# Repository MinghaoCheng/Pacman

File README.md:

# Pacman
ENG5220, Embedded real-time programming project, Team19

|Author|Team 19|
|---|---
|E-mail|2359434c@student.gla.ac.uk

* The follwing link is two demostrations of playing the game, catched by the ghost and won the game
https://www.youtube.com/playlist?list=PLmhQhGby8E4eoPKThM3S1RnaBH7sxEcJI

## Motivation& Introduction

As a classic computer game, Pacman impressed lots of people. Now we can do a Pacman game in real life!

This project uses a game panel which contains two 4x4 LED matrices. One of them is in green working as Pacdots, and the other one is in red to represent the Ghost. There is also a 4x4 LDR matrix to give feedback to the host. Three matrices are on the same place and controlled by the host raspberryPi.

There is a car controlled by a raspberryPi which acts as Pacman. It can move around upon the pannel, eat Pacdots and hide from the Ghost.

## Table of contents
* [Getting started](#getting_started)
* [System overview](#system_overview)
* [Required components(BOM)](#required_components(BOM))
* [Assemble](#assemble)
* [Software](#software)
* [Found a bug](#found_a_bug)
* [License](#license)
## Getting started 
1. Buiding hardware  
      Hardware contains PCBs, mechanics, sodering, see [Hardware](#hardware) for details.  
2. Built& install software  
    1. Host  
      To build the software of host: on host raspberryPi, type ```./build_host.sh``` in terminal.  
      To install the software of host:type ```sudo ./install_host.sh``` in terminal. (Only the kernel module needs to be installed)  
    2. Car  
      To build the software of car: on car raspberryPi, type ```./build_car.sh``` in terminal.
3. Execute the programme  
    1. Host  
      Type "sudo ./host_exe" in terminal. (Because this programme would access the kernel module, so it requires super_user)  
    2. Car  
      Type "./car_exe" in terminal.
4. Game rules  
      Once the game starts(After the background music), the Pacdots(green LEDs) would all be on. The Pacman(the Car) would follow the instructions of keyboard connected to the host. If the Pacman eats a Pacdot (car hits the green LED), the LDR would give feedback to the host and shut down the corresponding LED. Meanwhile, a sound would give the player a feedback. The player would win the game when all Pacdots are eaten (a winning music would be played). There is only one ghost(red LED), which would move randomly, if the Pacman hits the ghost, the player will lose (a losing music would be played).  
5. Have fun!  

## System overview
* This project contains a host and a car. The host does the following work:  
    ** Control a red LED matrix using a GPIO extender "MCP23S17" to display the location of the ghost
    ** Control a green LED matrix using a GPIO extender "MCP23S17" to display the pacdots
    ** Control a LDR matrix as the feedback of location of the car
    ** Handle a TCP/IP connection as the server, and send instructions to the car via the connection
    ** Connect with a simple keyboard as input
    ** Output sound through 3.5mm audio jack (Using function "system()" now, I would add ALSA sound driver later)  
* The car work as follow:
    ** Handle a TCP/IP connection as client to receive instructions from the host
    ** Control two motors(which drive the wheels of the car) through a dual H-bridge IC "L298N"
    ** The car sink current from 4xAA batteries and a 5V3A LDO is used.

## Required components(BOM)
* host_0 board

|Component|Quantity|Farnell code|
|---|---|---
|4816P-T02-222LF|1|2908136
|LM2901D|4|1648673
|Resistor,2kΩ,R0805|1|1469887
|Resistor,10kΩ,R0805|2|1469856
|MCP23S17T-E/SS|1|2775058
|pin header 2x8, bended, 2.54mm|2|2984492
|Capacitor, 0.1uF, C0603|1|2280842
|M20-6102045,Connector|1|1569230

* host_1 board

|Component|Quantity|Farnell code|
|---|---|---
|MCP23S17T-E/SS|1|2775058
|BCW66GLT1G|4|2317524
|BCW68GLT1G|4|2317538
|4816P-1-102LF|2|1612549
|M20-6102045,Connector|1|1569230
|pin header 2x8, bended, 2.54mm|1|2984492
|Capacitor, 0.1uF, C0603|1|2280842
|Resistor,200Ω,R0805*|8|1894175

    *:optional,depends on the impedence of the LEDs  

* car_0 board

|Component|Quantity|Farnell code|
|---|---|---
|L298N|1|403295
|NCP59301DS50R4G|1|2774711
|BYG10M-E3/TR|8|9549170
|Capacitor, 0.1uF, C0805|2|

* Others

|Component|Quantity|Farnell code|
|---|---|---
|RapsberryPi model 3B|2|
|Green LED*|16|
|Red LED*|16|
|LDR|16|3168335
|Wires|N/A|
|Panel**|1|

    *:could use any LEDs under 100mA, but the resistors on host_1 board needs to be adjusted  
    **:In this project, the panel was made of a cardboard.
## Assemble
* For PCBs of the host, connect them in the way as follow:  

<div align=center></div>  

<div align=center></div>  

* For LED&LDR matrices, put one green LED, one red LED and one LDR at a single hole on the panel(There are 4x4 holes). Note to put LDR above the LEDs.  

<div align=center></div>  

* Solder green LED matrix/red LED matrix as follow, this schematic also can be found at [PCBs](/Docs/PCBs):

<div align=center></div> 

* Solder keyboard following the schematic

* Picture of the system set

<div align=center></div>

<div align=center></div>

## Software
* There are two source codes in this project. One works on the host and another one works on the car.  
* The software of the host contains a kernel module which would work as the driver of the GPIO(it handles GPIO interrupt and output of the GPIO used by the host), and it contains the main codes which works in the user space. There are several components of this software, see details at [Docs](/Docs/software/host)  
* The software of the car controls the motor using L298N through GPIO, and it also receives instructions from the host over TCP/IP through Wi-Fi connection. See details at [Docs](/Docs/software/car)   
* dependency:  
      * host:
      ```pthread, rt, ```
      * car:
      ```pthread```
## Found a bug<a name="found_a_bug">
* Hardware:  
      To isolate the fault of the hardware, the best way is to check the PCB-layouts and schematics.  
      Here is the definition of pins used by the host:  
      
|Raspi-pin|Function|
|---|---
|03|Reset of MCP23S17(s)
|05|INT B of MCP23S17 of LDR board
|07|INT A of MCP23S17 of LDR board
|19|MOSI of SPI bus
|21|MISO of SPI bus
|23|CLK of SPI bus
|24|CS_0 of SPI bus, LDR board
|26|CS_1 of SPI bus, LED board
|29|Keyboard, Left
|31|Keyboard, Up
|33|Keyboard, Right
|35|Keyboard, Down
|37|Keyboard, Reset
      
* Software:
      Remember to add "sudo" to install the host kernel module and execute the programme
      
* For other questions, you can send me an Email with description

## License
See license.md

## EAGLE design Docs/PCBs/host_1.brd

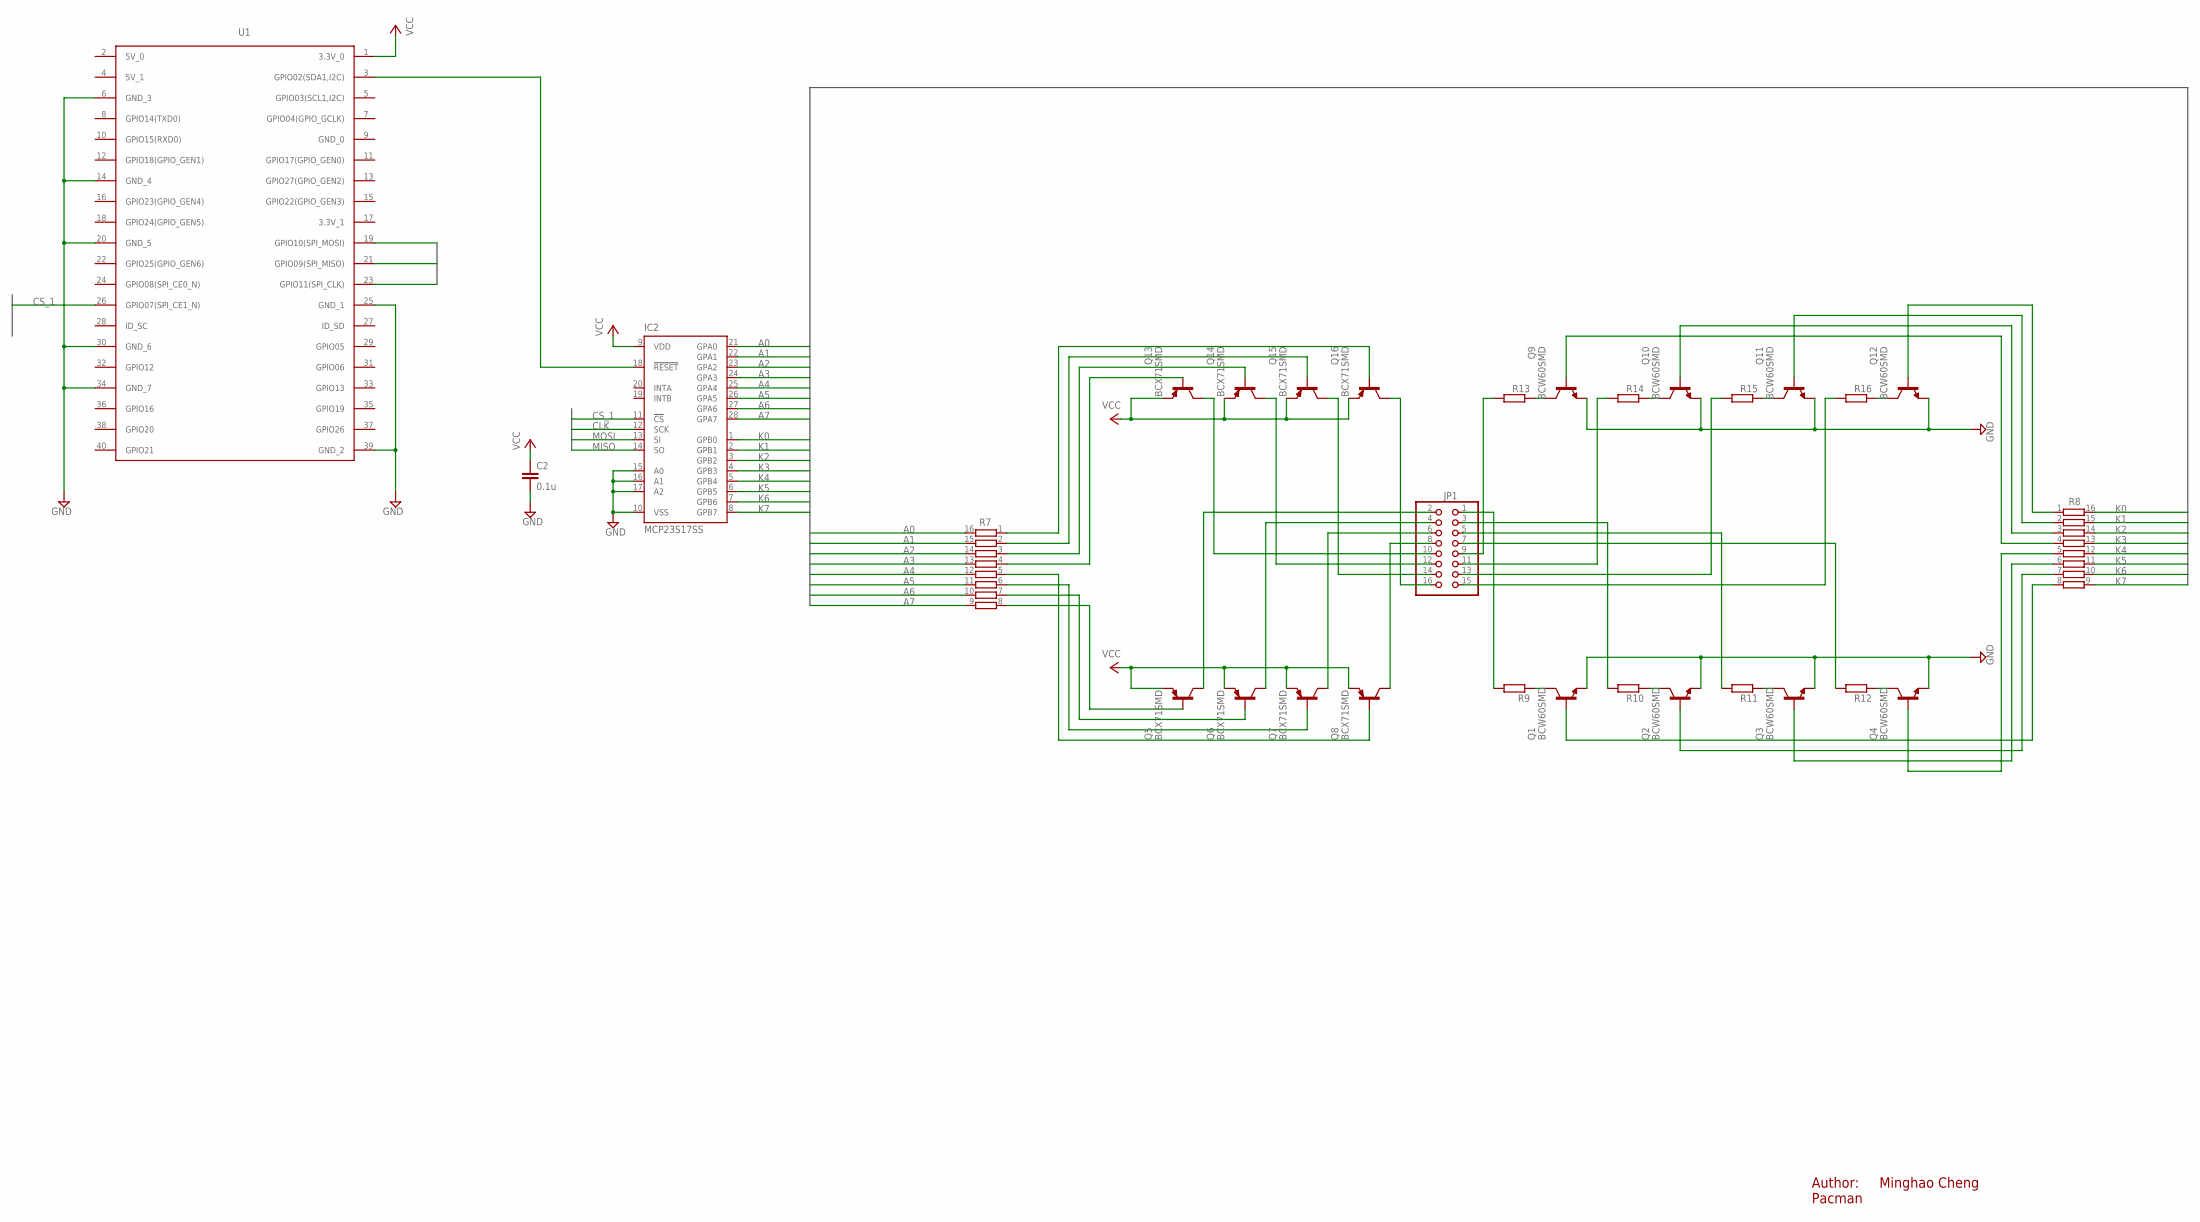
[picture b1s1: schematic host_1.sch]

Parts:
C2: 0.1u; C0805
IC2: MCP23S17SS; SSOP28
JP1: PINHD-2X8; 2X08
Q1, Q2, Q3, Q4, Q9, Q10, Q11, Q12: BCW60SMD; SOT23-BEC
Q5, Q6, Q7, Q8, Q13, Q14, Q15, Q16: BCX71SMD; SOT23
R7, R8: 4816P-T01; 4816P
R9, R10, R11, R12, R13, R14, R15, R16: 4.7K; R0805
U1: RASPI3_GPIO; FE20-2

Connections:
A0: IC2.21 (GPA0), R7.16
A1: IC2.22 (GPA1), R7.15
A2: IC2.23 (GPA2), R7.14
A3: IC2.24 (GPA3), R7.13
A4: IC2.25 (GPA4), R7.12
A5: IC2.26 (GPA5), R7.11
A6: IC2.27 (GPA6), R7.10
A7: IC2.28 (GPA7), R7.9
CLK: IC2.12 (SCK), U1.23 (GPIO11(SPI_CLK))
CS_1: IC2.11 (!CS), U1.26 (GPIO07(SPI_CE1_N))
GND: C2.2, IC2.10 (VSS), IC2.15 (A0), IC2.16 (A1), IC2.17 (A2), Q1.E, Q2.E, Q3.E, Q4.E, Q9.E, Q10.E, Q11.E, Q12.E, U1.6 (GND_3), U1.14 (GND_4), U1.20 (GND_5), U1.25 (GND_1), U1.30 (GND_6), U1.34 (GND_7), U1.39 (GND_2)
K0: IC2.1 (GPB0), R8.16
K1: IC2.2 (GPB1), R8.15
K2: IC2.3 (GPB2), R8.14
K3: IC2.4 (GPB3), R8.13
K4: IC2.5 (GPB4), R8.12
K5: IC2.6 (GPB5), R8.11
K6: IC2.7 (GPB6), R8.10
K7: IC2.8 (GPB7), R8.9
MISO: IC2.14 (SO), U1.21 (GPIO09(SPI_MISO))
MOSI: IC2.13 (SI), U1.19 (GPIO10(SPI_MOSI))
unnamed: IC2.18 (!RESET), U1.3 (GPIO02(SDA1,I2C))
unnamed: JP1.1, R9.2
unnamed: JP1.3, R10.2
unnamed: JP1.5, R11.2
unnamed: Q5.1 (B), R7.8
unnamed: JP1.7, R12.2
unnamed: JP1.9, R13.2
unnamed: JP1.11, R14.2
unnamed: JP1.13, R15.2
unnamed: JP1.15, R16.2
unnamed: JP1.2, Q5.3 (C)
unnamed: JP1.4, Q6.3 (C)
unnamed: JP1.6, Q7.3 (C)
unnamed: JP1.8, Q8.3 (C)
unnamed: JP1.10, Q13.3 (C)
unnamed: Q1.B, R8.8
unnamed: Q2.B, R8.7
unnamed: Q3.B, R8.6
unnamed: Q4.B, R8.5
unnamed: Q9.B, R8.4
unnamed: Q10.B, R8.3
unnamed: Q11.B, R8.2
unnamed: Q6.1 (B), R7.7
unnamed: Q7.1 (B), R7.6
unnamed: Q8.1 (B), R7.5
unnamed: JP1.12, Q14.3 (C)
unnamed: JP1.14, Q15.3 (C)
unnamed: JP1.16, Q16.3 (C)
unnamed: Q12.B, R8.1
unnamed: Q1.C, R9.1
unnamed: Q2.C, R10.1
unnamed: Q3.C, R11.1
unnamed: Q4.C, R12.1
unnamed: Q13.1 (B), R7.4
unnamed: Q14.1 (B), R7.3
unnamed: Q15.1 (B), R7.2
unnamed: Q16.1 (B), R7.1
unnamed: Q9.C, R13.1
unnamed: Q10.C, R14.1
unnamed: Q11.C, R15.1
unnamed: Q12.C, R16.1
VCC: C2.1, IC2.9 (VDD), Q5.2 (E), Q6.2 (E), Q7.2 (E), Q8.2 (E), Q13.2 (E), Q14.2 (E), Q15.2 (E), Q16.2 (E), U1.1 (3.3V_0)

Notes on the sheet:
Author: Minghao Cheng Pacman

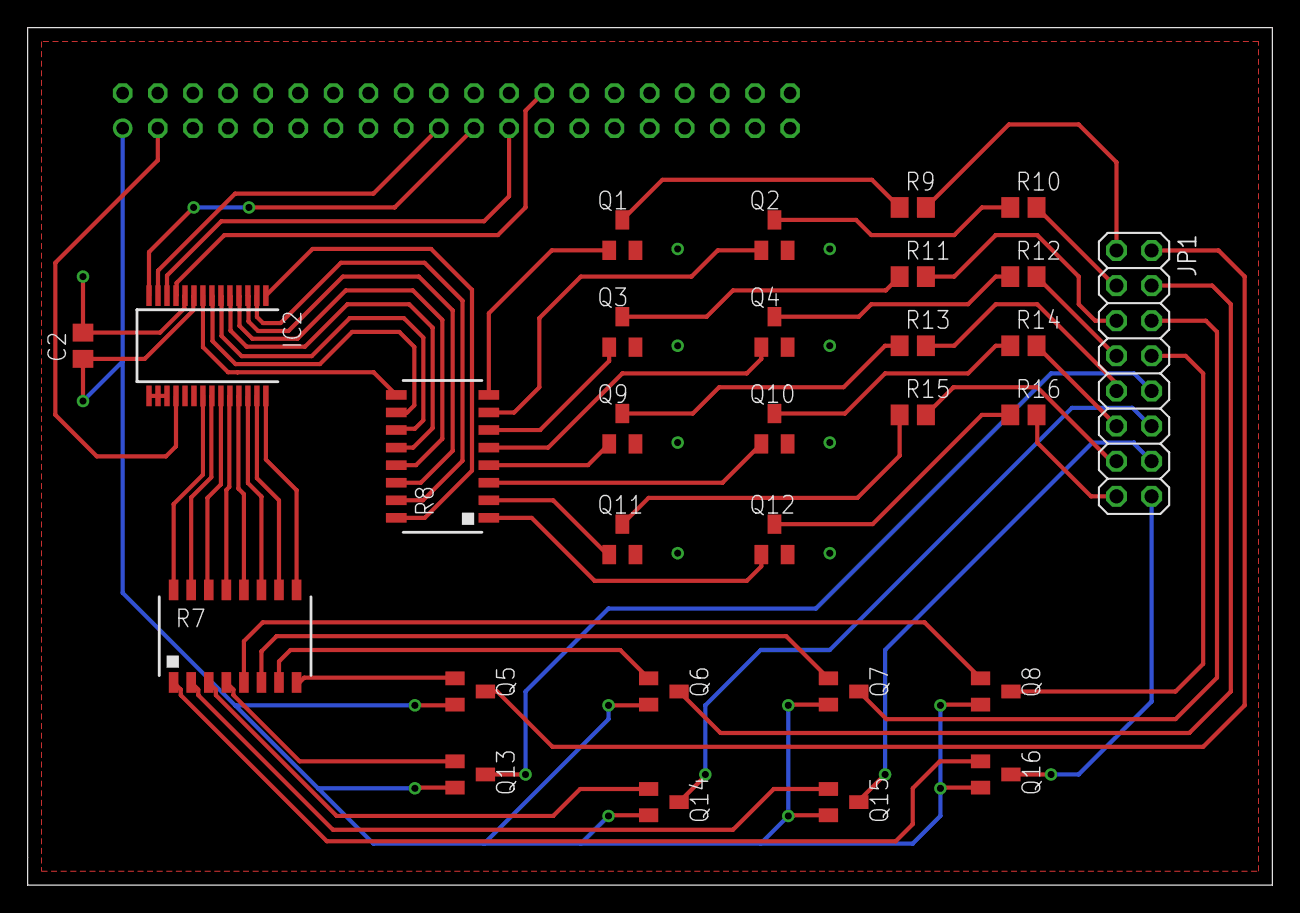
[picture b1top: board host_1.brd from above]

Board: 2 copper layers, 90.0 x 62.0 mm, 30 parts (1 on the bottom side), 63 nets.

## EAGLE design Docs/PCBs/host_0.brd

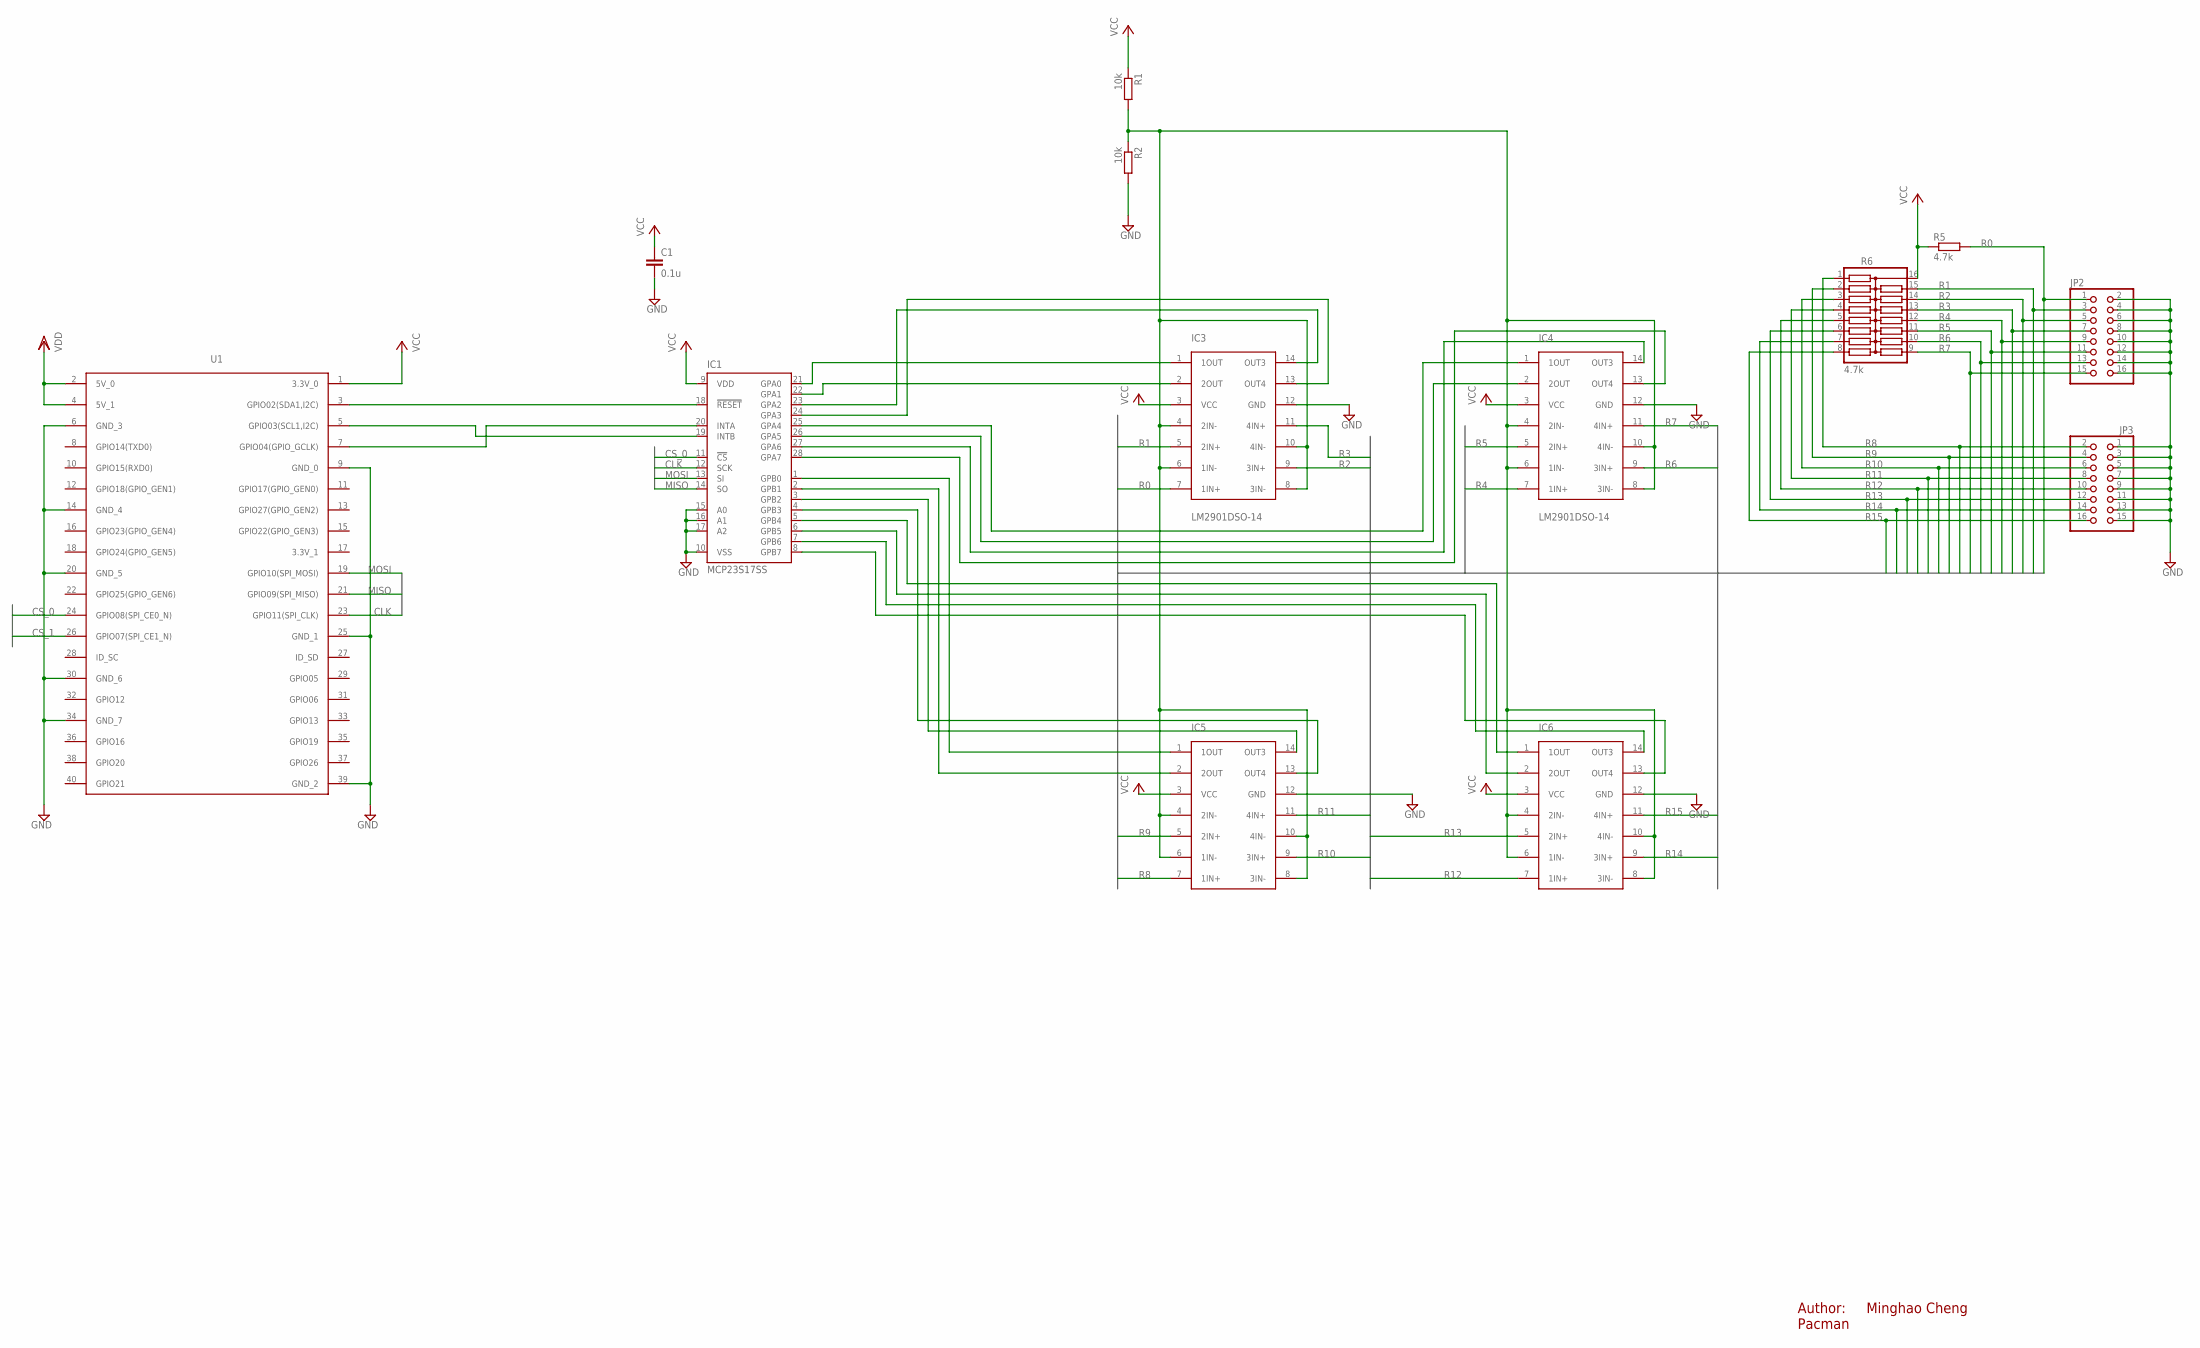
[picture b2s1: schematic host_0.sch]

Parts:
C1: 0.1u; C0805
IC1: MCP23S17SS; SSOP28
IC3, IC4, IC5, IC6: LM2901DSO-14; SO14
JP2, JP3: PINHD-2X8; 2X08
R1, R2: 10k; R0805
R5: 4.7k; R0805
R6: 4.7k; 4816P
U1: RASPI3_GPIO; FE20-2

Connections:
CLK: IC1.12 (SCK), U1.23 (GPIO11(SPI_CLK))
CS_0: IC1.11 (!CS), U1.24 (GPIO08(SPI_CE0_N))
CS_1: U1.26 (GPIO07(SPI_CE1_N))
GND: C1.2, IC1.10 (VSS), IC1.15 (A0), IC1.16 (A1), IC1.17 (A2), IC3.12 (GND), IC4.12 (GND), IC5.12 (GND), IC6.12 (GND), JP2.2, JP2.4, JP2.6, JP2.8, JP2.10, JP2.12, JP2.14, JP2.16, JP3.1, JP3.3, JP3.5, JP3.7, JP3.9, JP3.11, JP3.13, JP3.15, R2.2, U1.6 (GND_3), U1.9 (GND_0), U1.14 (GND_4), U1.20 (GND_5), U1.25 (GND_1), U1.30 (GND_6), U1.34 (GND_7), U1.39 (GND_2)
MISO: IC1.14 (SO), U1.21 (GPIO09(SPI_MISO))
MOSI: IC1.13 (SI), U1.19 (GPIO10(SPI_MOSI))
unnamed: IC1.18 (!RESET), U1.3 (GPIO02(SDA1,I2C))
unnamed: IC1.20 (INTA), U1.7 (GPIO04(GPIO_GCLK))
unnamed: IC1.19 (INTB), U1.5 (GPIO03(SCL1,I2C))
unnamed: IC1.23 (GPA2), IC3.14 (OUT3)
unnamed: IC1.24 (GPA3), IC3.13 (OUT4)
unnamed: IC3.4 (2IN-), IC3.6 (1IN-), IC3.8 (3IN-), IC3.10 (4IN-), IC4.4 (2IN-), IC4.6 (1IN-), IC4.8 (3IN-), IC4.10 (4IN-), IC5.4 (2IN-), IC5.6 (1IN-), IC5.8 (3IN-), IC5.10 (4IN-), IC6.4 (2IN-), IC6.6 (1IN-), IC6.8 (3IN-), IC6.10 (4IN-), R1.2, R2.1
unnamed: IC1.21 (GPA0), IC3.1 (1OUT)
unnamed: IC1.22 (GPA1), IC3.2 (2OUT)
unnamed: IC1.25 (GPA4), IC4.1 (1OUT)
unnamed: IC1.26 (GPA5), IC4.2 (2OUT)
unnamed: IC1.27 (GPA6), IC4.14 (OUT3)
unnamed: IC1.28 (GPA7), IC4.13 (OUT4)
unnamed: IC1.1 (GPB0), IC5.1 (1OUT)
unnamed: IC1.2 (GPB1), IC5.2 (2OUT)
unnamed: IC1.3 (GPB2), IC5.14 (OUT3)
unnamed: IC1.5 (GPB4), IC6.1 (1OUT)
unnamed: IC1.4 (GPB3), IC5.13 (OUT4)
unnamed: IC1.6 (GPB5), IC6.2 (2OUT)
unnamed: IC1.7 (GPB6), IC6.14 (OUT3)
unnamed: IC1.8 (GPB7), IC6.13 (OUT4)
R0: IC3.7 (1IN+), JP2.1, R5.2
R1: IC3.5 (2IN+), JP2.3, R6.15
R2: IC3.9 (3IN+), JP2.5, R6.14
R3: IC3.11 (4IN+), JP2.7, R6.13
R4: IC4.7 (1IN+), JP2.9, R6.12
R5: IC4.5 (2IN+), JP2.11, R6.11
R6: IC4.9 (3IN+), JP2.13, R6.10
R7: IC4.11 (4IN+), JP2.15, R6.9
R8: IC5.7 (1IN+), JP3.2, R6.1
R9: IC5.5 (2IN+), JP3.4, R6.2
R10: IC5.9 (3IN+), JP3.6, R6.3
R11: IC5.11 (4IN+), JP3.8, R6.4
R12: IC6.7 (1IN+), JP3.10, R6.5
R13: IC6.5 (2IN+), JP3.12, R6.6
R14: IC6.9 (3IN+), JP3.14, R6.7
R15: IC6.11 (4IN+), JP3.16, R6.8
VCC: C1.1, IC1.9 (VDD), IC3.3 (VCC), IC4.3 (VCC), IC5.3 (VCC), IC6.3 (VCC), R1.1, R5.1, R6.16, U1.1 (3.3V_0)
VDD: U1.2 (5V_0), U1.4 (5V_1)

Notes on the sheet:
Author: Minghao Cheng Pacman

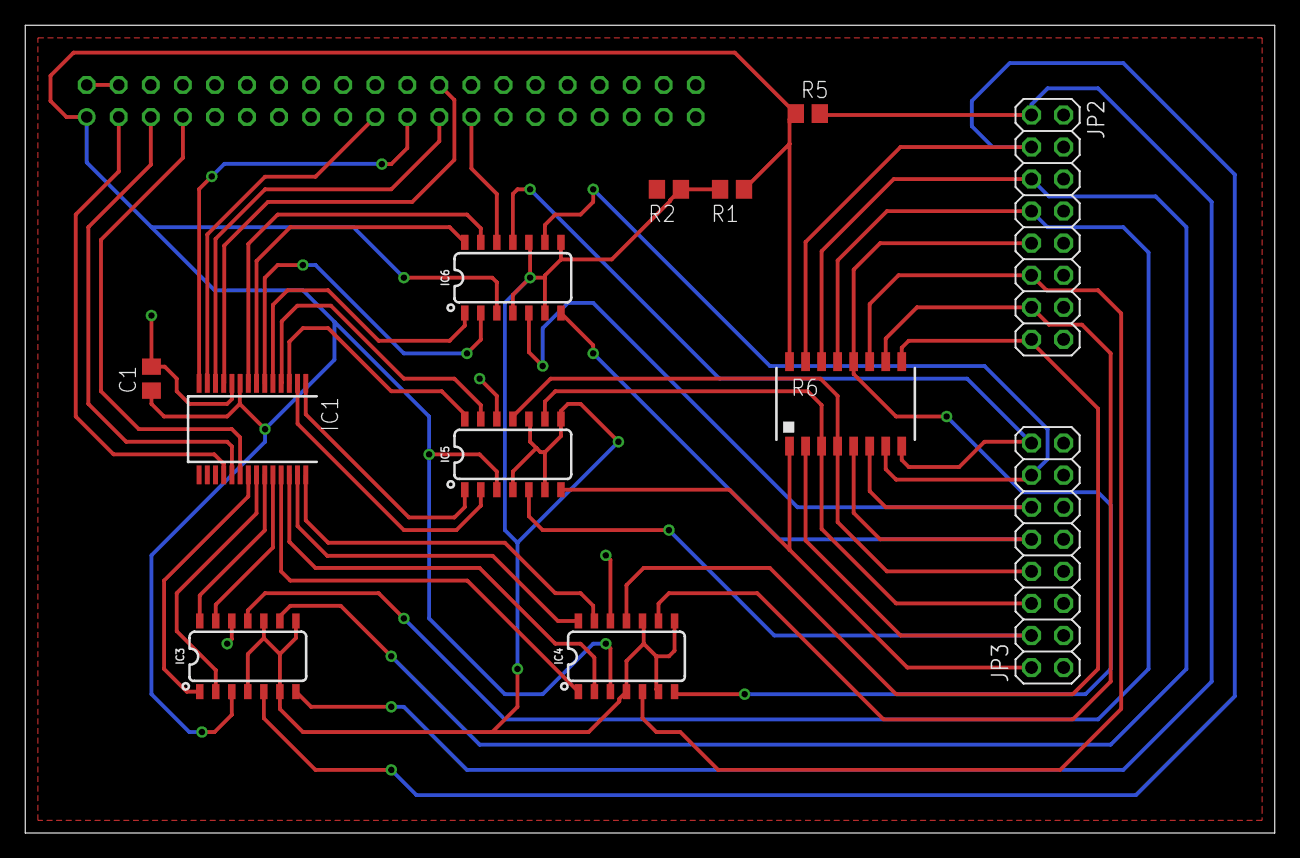
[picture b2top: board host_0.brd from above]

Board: 2 copper layers, 99.0 x 64.0 mm, 13 parts (1 on the bottom side), 43 nets.

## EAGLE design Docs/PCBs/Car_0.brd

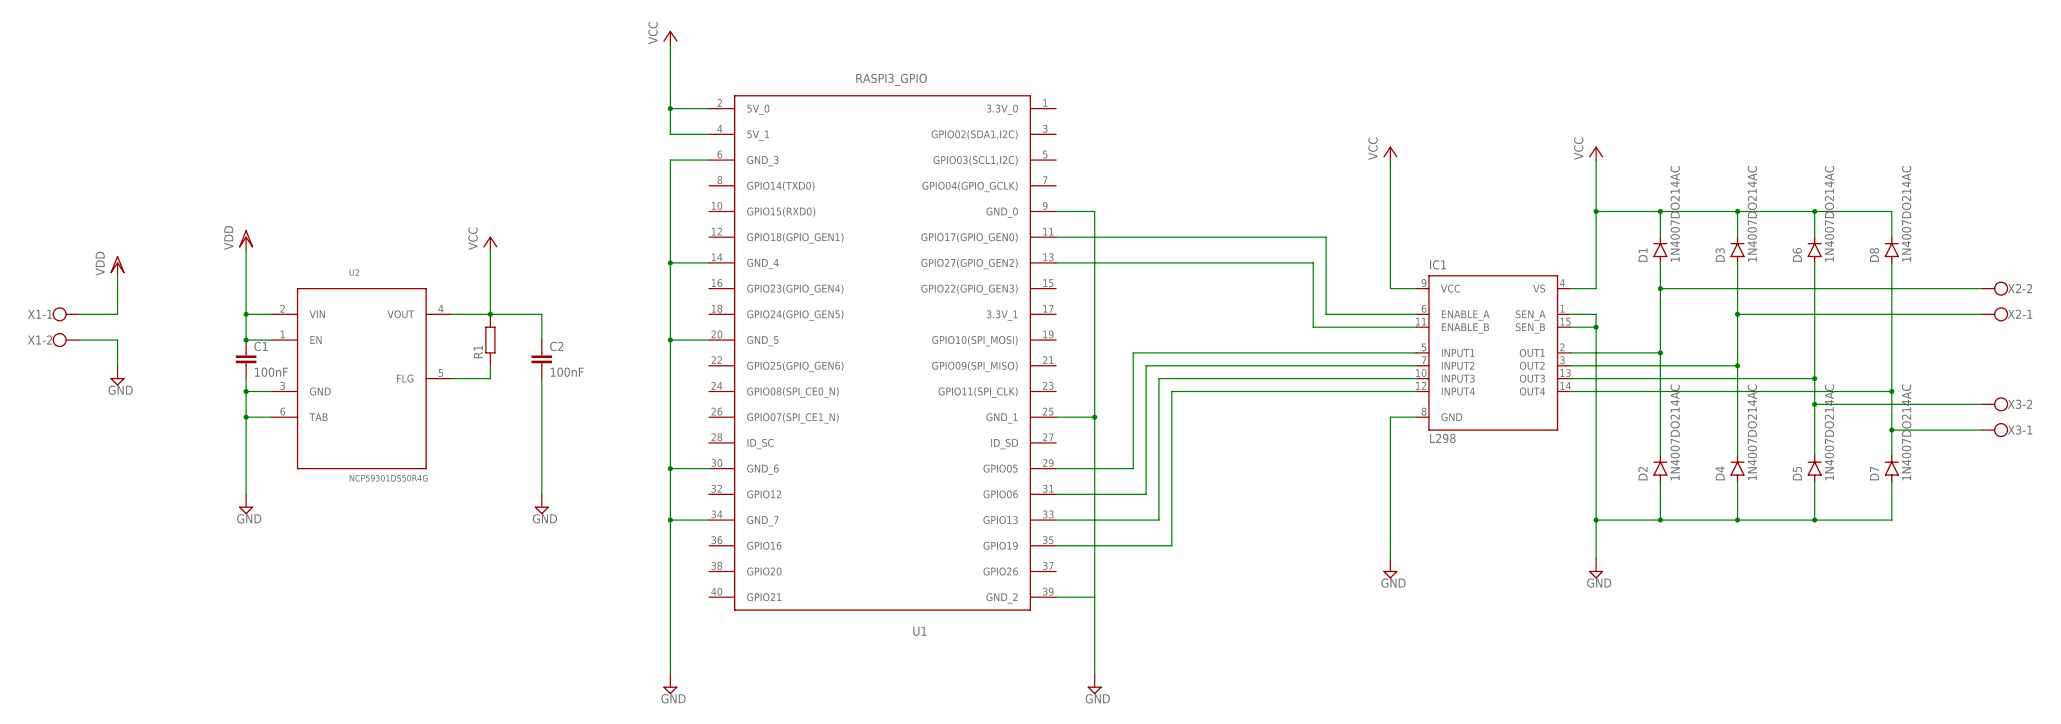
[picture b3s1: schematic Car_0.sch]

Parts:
C1, C2: 100nF; C0805
D1, D2, D3, D4, D5, D6, D7, D8: 1N4007DO214AC; SMA-DO214AC
IC1: L298; MULTIWATT-15
R1: R-EU_R0805; R0805
U1: RASPI3_GPIO; FE20-2
U2: NCP59301DS50R4G; TO263-5
X1, X2, X3: W237-102

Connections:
GND: C1.2, C2.2, D2.A, D4.A, D5.A, D7.A, IC1.1 (SEN_A), IC1.8 (GND), IC1.15 (SEN_B), U1.6 (GND_3), U1.9 (GND_0), U1.14 (GND_4), U1.20 (GND_5), U1.25 (GND_1), U1.30 (GND_6), U1.34 (GND_7), U1.39 (GND_2), U2.3 (GND), U2.6 (TAB), X1.2
unnamed: D1.A, D2.K (C), IC1.2 (OUT1), X2.2
unnamed: D3.A, D4.K (C), IC1.3 (OUT2), X2.1
unnamed: D5.K (C), D6.A, IC1.13 (OUT3), X3.2
unnamed: D7.K (C), D8.A, IC1.14 (OUT4), X3.1
unnamed: IC1.6 (ENABLE_A), U1.11 (GPIO17(GPIO_GEN0))
unnamed: IC1.11 (ENABLE_B), U1.13 (GPIO27(GPIO_GEN2))
unnamed: IC1.5 (INPUT1), U1.29 (GPIO05)
unnamed: IC1.7 (INPUT2), U1.31 (GPIO06)
unnamed: IC1.10 (INPUT3), U1.33 (GPIO13)
unnamed: IC1.12 (INPUT4), U1.35 (GPIO19)
unnamed: R1.1, U2.5 (FLG)
VCC: C2.1, D1.K (C), D3.K (C), D6.K (C), D8.K (C), IC1.4 (VS), IC1.9 (VCC), R1.2, U1.2 (5V_0), U1.4 (5V_1), U2.4 (VOUT)
VDD: C1.1, U2.1 (EN), U2.2 (VIN), X1.1

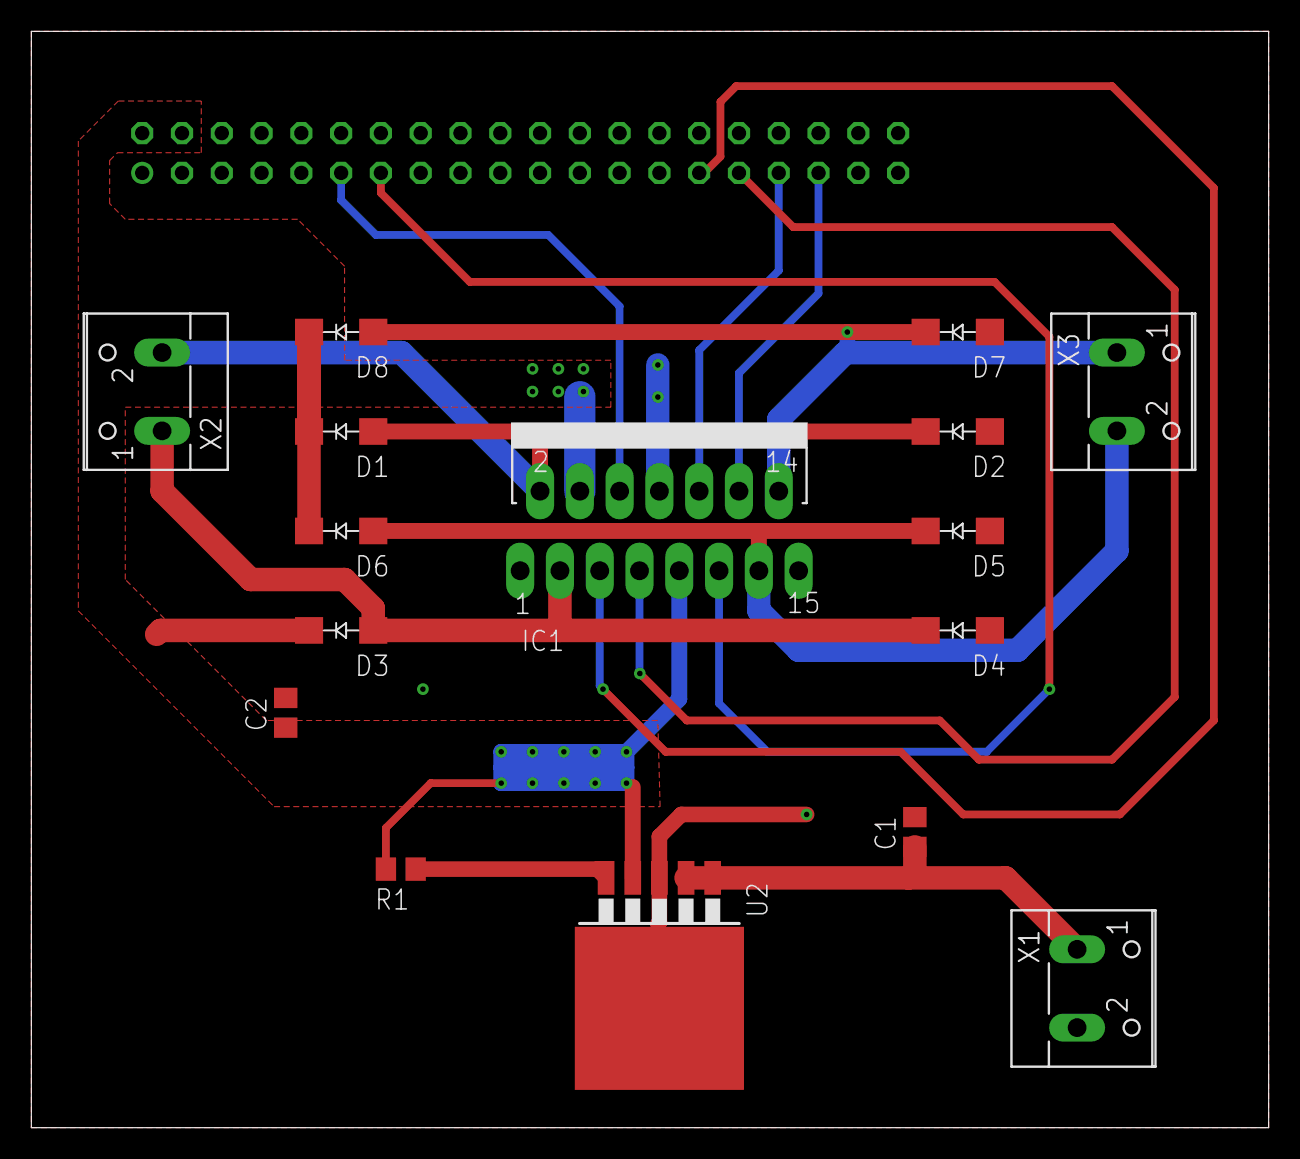
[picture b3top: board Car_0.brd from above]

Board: 2 copper layers, 79.0 x 70.0 mm, 17 parts (1 on the bottom side), 14 nets.

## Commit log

2019-01-21 testing
2019-01-21 TEST
2019-01-21 cmake testing
2019-01-23 CMakefile update
2019-01-30 team 19
2019-01-30 xx updated
2019-01-30 host added
2019-01-30 cmake clean bash
2019-01-30 cmake update
2019-02-09 implemented a simple kernel module for GPIO INT
2019-02-13 kernel module trim
2019-02-25 user space SPI driver added. MCP23s17 driver added, test version
2019-02-25 SPI/mcp23s17 drivers test version
2019-02-27 pthread class implementation
2019-03-05 thread class update
2019-03-16 kernelmodule update
2019-03-16 kernel mod update
2019-03-17 led matrix driver added
2019-03-18 readme update
2019-03-18 timer test update
2019-03-25 brd_1 test OK
2019-03-25 GPIO extender testing code added
2019-03-26 game hardware driver update
2019-03-28 LDR INT mapping, timer tested
2019-03-31 testing sound
2019-03-31 comments updated
2019-04-07 adapted to hardware
2019-04-09 Readme changed, updates with LED panel driver
2019-04-10 adapted to hardware, game logic control code updated
2019-04-10 general timer added
2019-04-10 kernel module updated
2019-04-10 CMake changed, bug fixed
2019-04-10 README updated
2019-04-10 LED_matrix schematic
2019-04-10 naming changed
2019-04-10 renamed sound files& added an install_host.sh
2019-04-11 bug fixed
2019-04-11 buiding bash updated
2019-04-11 build_host bash updated
2019-04-12 TCP/IP connection added
2019-04-13 keyboard added, files re-arranged
2019-04-13 Keyboard added, files rearranged
2019-04-13 in TCP, use poll()and recv() to check socket connection instead of read(), because of SIGRTMIN (SIG34) would interrupt the read() function (read() function is using select() inside)
2019-04-14 TCP/IP connection bug fixed
2019-04-14 small changes adapting to the hardware
2019-04-14 Keyboard sch added
2019-04-15 Doxygen docs added
2019-04-15 car software updated
2019-04-15 build script& Cmake added
